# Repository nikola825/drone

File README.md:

## 3D printable FPV quadcopter frame, SMT32-based flight controller and flight controller code

Hobby project, a homemade FPV drone with custom flight controller and frame.

### Current version - master branch
Folder contents (see readmes for more details):
- `3dp` - Freecad projects with 3D printable drone parts
- `code` - code for the flight controller
- `hardware` - KiCad projects for flight controller and esc PCB

Off the shelf parts you'll need:
- screws and screw related parts for the frame - see the readme in `3dp`
- motors and propellers
- ESC
- ELRS receiver
- Camera and VTX if you want FPV video

I couldn't be bothered to do in-detail docs, feel free to email me at (reverse the string to get my email) `moc.liamg@528alokin`

Do not use for anything serious, this was made by a man who started with zero knowledge of electronics, embedded development, rust development, flight controllers and 3D print design.
If you need something reliable, just get off-the-shelf stuff.

### Older versions
- `droneV1` branch contains the old Arduino-as-a-controller + MPU6050 version
- `droneV2` branch contains the old ATMEGA2560 flight controller board with an onboard MPU6050
- `droneV3` branch contains the work-in-progress version of the STM32F411 flight controller

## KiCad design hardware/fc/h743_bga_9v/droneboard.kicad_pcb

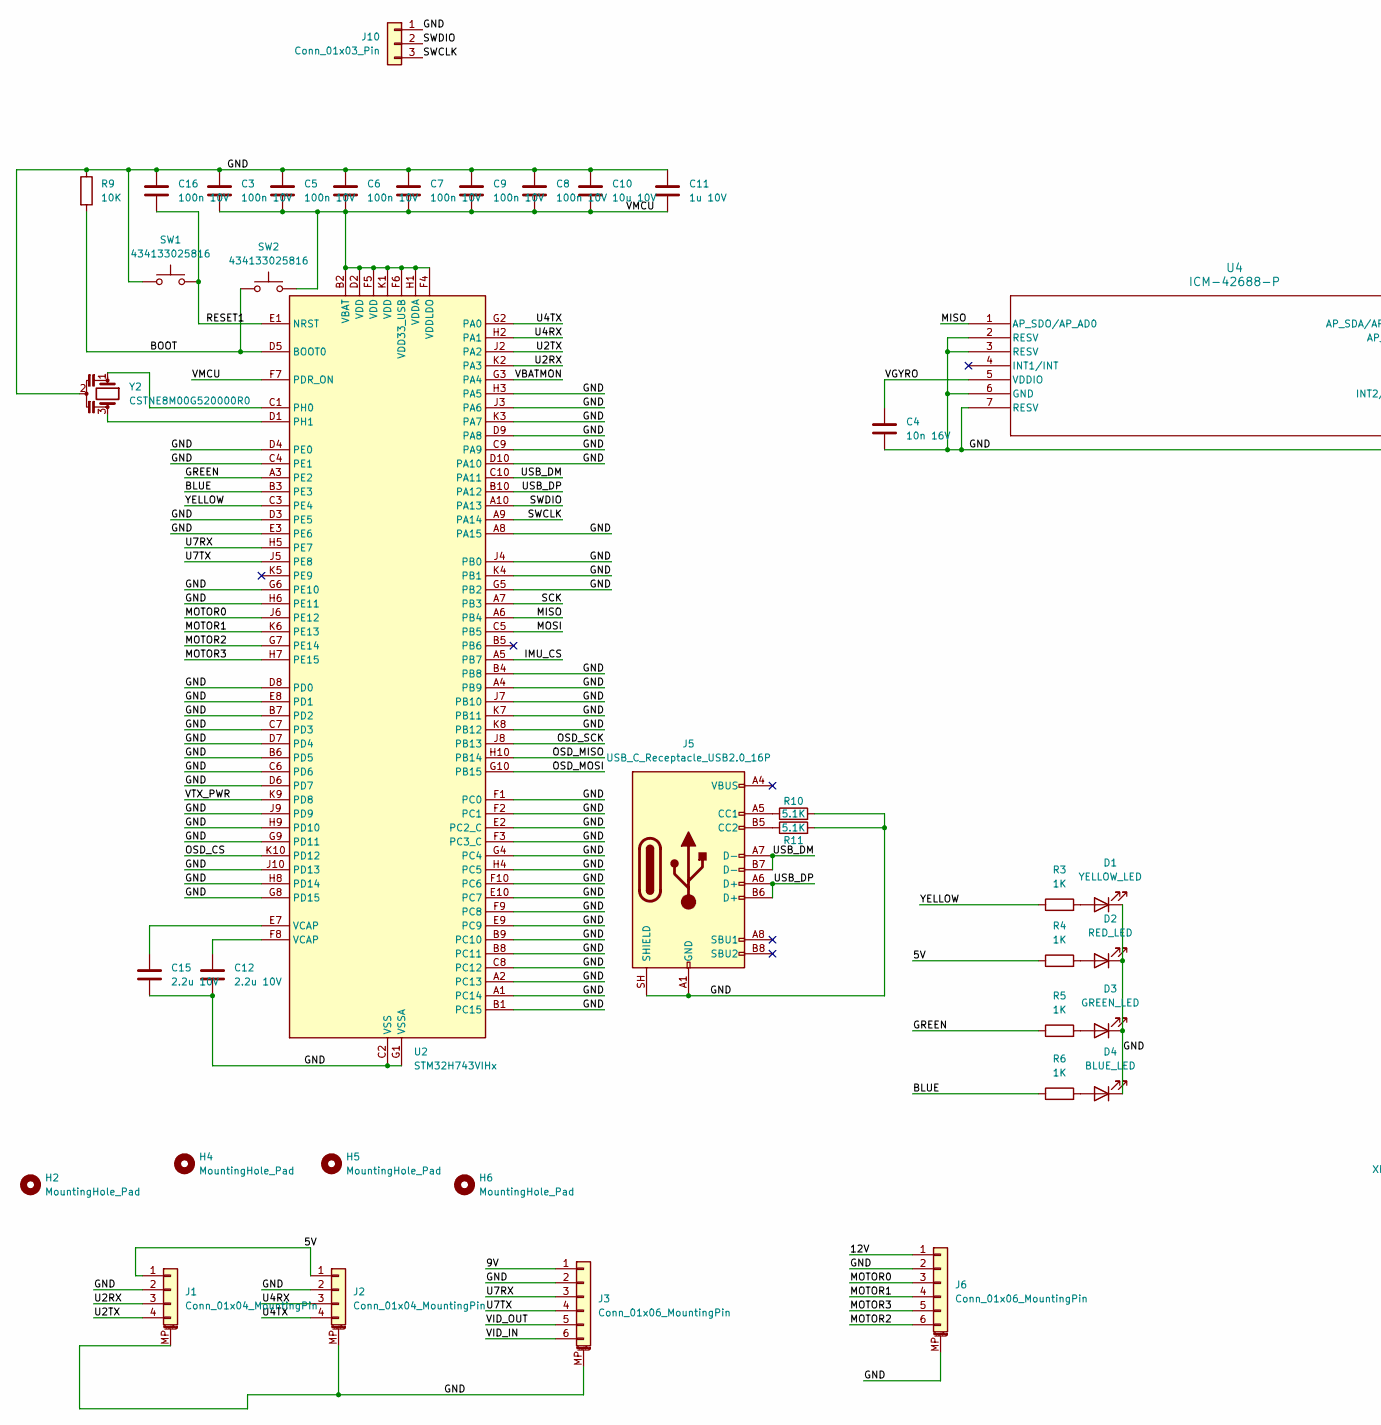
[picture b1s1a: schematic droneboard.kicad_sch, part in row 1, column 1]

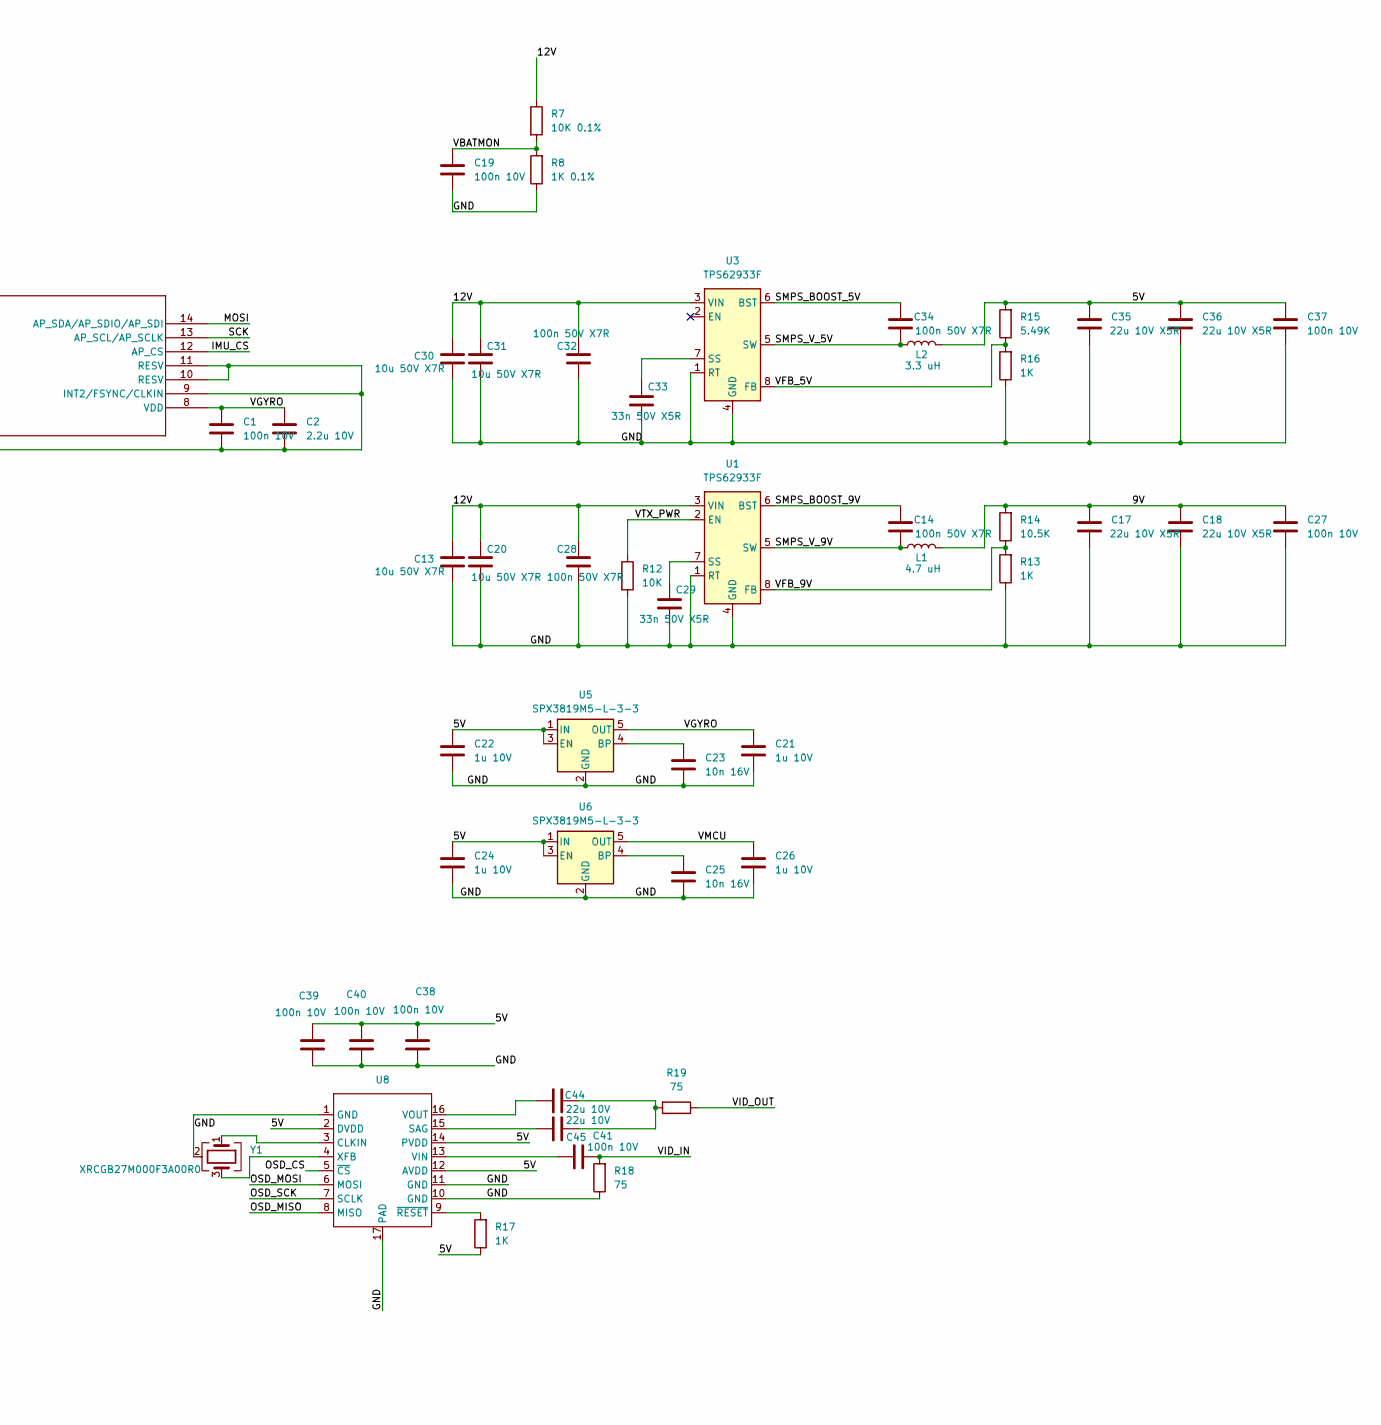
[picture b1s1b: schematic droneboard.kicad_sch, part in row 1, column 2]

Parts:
C1, C3, C5, C6, C7, C8, C9, C16, C19, C27, C37, C38, C39, C40, C41: 100n 10V; C_0201_0603Metric
C2, C12, C15: 2.2u 10V; C_0201_0603Metric
C4, C23, C25: 10n 16V; C_0201_0603Metric
C10: 10u 10V; C_0603_1608Metric
C11, C21, C22, C24, C26: 1u 10V; C_0201_0603Metric
C13, C20, C30, C31: 10u 50V X7R; C_1210_3225Metric
C14, C28, C32, C34: 100n 50V X7R; C_0402_1005Metric
C17, C18, C35, C36: 22u 10V X5R; C_0805_2012Metric
C29, C33: 33n 50V X5R; C_0402_1005Metric
C44, C45: 22u 10V; C_0603_1608Metric
D1: YELLOW_LED; LED_0603_1608Metric
D2: RED_LED; LED_0603_1608Metric
D3: GREEN_LED; LED_0603_1608Metric
D4: BLUE_LED; LED_0603_1608Metric
H2, H4, H5, H6: MountingHole_Pad; M3VibrationMount
J1, J2: Conn_01x04_MountingPin; JST_SH_SM04B-SRSS-TB_1x04-1MP_P1.00mm_Horizontal
J3, J6: Conn_01x06_MountingPin; JST_SH_SM06B-SRSS-TB_1x06-1MP_P1.00mm_Horizontal
J5: USB_C_Receptacle_USB2.0_16P; GCT_USB4110
J10: Conn_01x03_Pin; PinHeader_1x03_P2.00mm_Vertical
L1: 4.7 uH; L_Bourns_4040
L2: 3.3 uH; L_Bourns_4040
R3, R4, R5, R6, R13, R16, R17: 1K; R_0402_1005Metric
R7: 10K 0.1%; R_0603_1608Metric
R8: 1K 0.1%; R_0603_1608Metric
R9, R12: 10K; R_0201_0603Metric
R10, R11: 5.1K; R_0201_0603Metric
R14: 10.5K; R_0402_1005Metric
R15: 5.49K; R_0402_1005Metric
R18, R19: 75; R_0402_1005Metric
SW1, SW2: 434133025816; SW_Push_1P1T_NO_Vertical_Wuerth_434133025816
U1, U3: TPS62933F; SOT-583-8
U2: STM32H743VIHx; TFBGA-100_8x8mm_Layout10x10_P0.8mm
U4: ICM-42688-P; ICM42688_Custom
U5, U6: SPX3819M5-L-3-3; SOT-23-5
U8: AT7456ELAH
Y1: XRCGB27M000F3A00R0; Crystal_SMD_2016-4Pin_2.0x1.6mm
Y2: CSTNE8M00G520000R0; Resonator_SMD_Murata_CSTxExxV-3Pin_3.0x1.1mm

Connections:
/5V: C22.1, C24.1, C35.1, C36.1, C37.2, C38.2, C39.2, C40.2, J1.1, J2.1, L2.2, R4.1, R15.2, R17.1, U5.1 (IN), U5.3 (EN), U6.1 (IN), U6.3 (EN), U8.2 (DVDD), U8.12 (AVDD), U8.14 (PVDD)
/9V: C17.1, C18.1, C27.2, J3.1, L1.2, R14.2
/12V: C13.1, C20.1, C28.2, C30.1, C31.1, C32.2, J6.1, R7.1, U1.3 (VIN), U3.3 (VIN)
/BLUE: R6.1, U2.B3 (PE3)
/BOOT: R9.2, SW2.1, U2.D5 (BOOT0)
/GND: C1.1, C2.2, C3.2, C4.1, C5.2, C6.2, C7.2, C8.2, C9.2, C10.1, C11.1, C12.2, C13.2, C15.2, C16.2, C17.2, C18.2, C19.1, C20.2, C21.2, C22.2, C23.1, C24.2, C25.1, C26.2, C27.1, C28.1, C29.1, C30.2, C31.2, C32.1, C33.1, C35.2, C36.2, C37.1, C38.1, C39.1, C40.1, D1.1 (K), D2.1 (K), D3.1 (K), D4.1 (K), J1.2, J1.MP (MountPin), J2.2, J2.MP (MountPin), J3.2, J3.MP (MountPin), J5.A1 (GND), J5.A12 (GND), J5.B1 (GND), J5.B12 (GND), J5.SH (SHIELD), J6.2, J6.MP (MountPin), J10.1, R8.1, R9.1, R10.2, R11.2, R12.2, R13.1, R16.1, R18.1, SW1.2, U1.1 (RT), U1.4 (GND), U2.A1 (PC14), U2.A2 (PC13), U2.A4 (PB9), U2.A8 (PA15), U2.B1 (PC15), U2.B4 (PB8), U2.B6 (PD5), U2.B7 (PD2), U2.B8 (PC11), U2.B9 (PC10), U2.C2 (VSS), U2.C4 (PE1), U2.C6 (PD6), U2.C7 (PD3), U2.C8 (PC12), U2.C9 (PA9), U2.D3 (PE5), U2.D4 (PE0), U2.D6 (PD7), U2.D7 (PD4), U2.D8 (PD0), U2.D9 (PA8), U2.D10 (PA10), U2.E2 (PC2_C), U2.E3 (PE6), U2.E4 (VSS), U2.E5 (VSS), U2.E6 (VSS), U2.E8 (PD1), U2.E9 (PC9), U2.E10 (PC7), U2.F1 (PC0), U2.F2 (PC1), U2.F3 (PC3_C), U2.F9 (PC8), U2.F10 (PC6), U2.G1 (VSSA), U2.G4 (PC4), U2.G5 (PB2), U2.G6 (PE10), U2.G8 (PD15), U2.G9 (PD11), U2.H3 (PA5), U2.H4 (PC5), U2.H6 (PE11), U2.H8 (PD14), U2.H9 (PD10), U2.J1 (VSS), U2.J3 (PA6), U2.J4 (PB0), U2.J7 (PB10), U2.J9 (PD9), U2.J10 (PD13), U2.K3 (PA7), U2.K4 (PB1), U2.K7 (PB11), U2.K8 (PB12), U3.1 (RT), U3.4 (GND), U4.2 (RESV), U4.3 (RESV), U4.6 (GND), U4.7 (RESV), U4.9 (INT2/FSYNC/CLKIN), U4.10 (RESV), U4.11 (RESV), U5.2 (GND), U6.2 (GND), U8.1 (GND), U8.10 (GND), U8.11 (GND), U8.17 (PAD), Y1.2 (G), Y1.4 (G), Y2.2
/GREEN: R5.1, U2.A3 (PE2)
/IMU_CS: U2.A5 (PB7), U4.12 (AP_CS)
/MISO: U2.A6 (PB4), U4.1 (AP_SDO/AP_AD0)
/MOSI: U2.C5 (PB5), U4.14 (AP_SDA/AP_SDIO/AP_SDI)
/MOTOR0: J6.3, U2.J6 (PE12)
/MOTOR1: J6.4, U2.K6 (PE13)
/MOTOR2: J6.6, U2.G7 (PE14)
/MOTOR3: J6.5, U2.H7 (PE15)
/OSD_CS: U2.K10 (PD12), U8.5 (~CS)
/OSD_MISO: U2.H10 (PB14), U8.8 (MISO)
/OSD_MOSI: U2.G10 (PB15), U8.6 (MOSI)
/OSD_SCK: U2.J8 (PB13), U8.7 (SCLK)
/RESET1: C16.1, SW1.1, U2.E1 (NRST)
/SCK: U2.A7 (PB3), U4.13 (AP_SCL/AP_SCLK)
/SMPS_BOOST_5V: C34.2, U3.6 (BST)
/SMPS_BOOST_9V: C14.2, U1.6 (BST)
/SMPS_V_5V: C34.1, L2.1, U3.5 (SW)
/SMPS_V_9V: C14.1, L1.1, U1.5 (SW)
/SWCLK: J10.3, U2.A9 (PA14)
/SWDIO: J10.2, U2.A10 (PA13)
/U2RX: J1.3, U2.K2 (PA3)
/U2TX: J1.4, U2.J2 (PA2)
/U4RX: J2.3, U2.H2 (PA1)
/U4TX: J2.4, U2.G2 (PA0)
/U7RX: J3.3, U2.H5 (PE7)
/U7TX: J3.4, U2.J5 (PE8)
/USB_DM: J5.A7 (D-), J5.B7 (D-), U2.C10 (PA11)
/USB_DP: J5.A6 (D+), J5.B6 (D+), U2.B10 (PA12)
/VBATMON: C19.2, R7.2, R8.2, U2.G3 (PA4)
/VFB_5V: R15.1, R16.2, U3.8 (FB)
/VFB_9V: R13.2, R14.1, U1.8 (FB)
/VGYRO: C1.2, C2.1, C4.2, C21.1, U4.5 (VDDIO), U4.8 (VDD), U5.5 (OUT)
/VID_IN: C41.1, J3.6, R18.2
/VID_OUT: J3.5, R19.1
/VMCU: C3.1, C5.1, C6.1, C7.1, C8.1, C9.1, C10.2, C11.2, C26.1, SW2.2, U2.B2 (VBAT), U2.D2 (VDD), U2.F4 (VDDLDO), U2.F5 (VDD), U2.F6 (VDD33_USB), U2.F7 (PDR_ON), U2.H1 (VDDA), U2.K1 (VDD), U6.5 (OUT)
/VTX_PWR: R12.1, U1.2 (EN), U2.K9 (PD8)
/YELLOW: R3.1, U2.C3 (PE4)
unnamed: C12.1, U2.F8 (VCAP)
unnamed: C15.1, U2.E7 (VCAP)
unnamed: C44.2, C45.2, R19.2
unnamed: D1.2 (A), R3.2
unnamed: D2.2 (A), R4.2
unnamed: D3.2 (A), R5.2
unnamed: D4.2 (A), R6.2
unnamed: J5.A5 (CC1), R10.1
unnamed: J5.B5 (CC2), R11.1
unnamed: C29.2, U1.7 (SS)
unnamed: U2.C1 (PH0), Y2.1
unnamed: U2.D1 (PH1), Y2.3
unnamed: C33.2, U3.7 (SS)
unnamed: C23.2, U5.4 (BP)
unnamed: C25.2, U6.4 (BP)
unnamed: U8.3 (CLKIN), Y1.1
unnamed: C45.1, U8.15 (SAG)
unnamed: C41.2, U8.13 (VIN)
unnamed: C44.1, U8.16 (VOUT)
unnamed: U8.4 (XFB), Y1.3
unnamed: R17.2, U8.9 (~RESET)

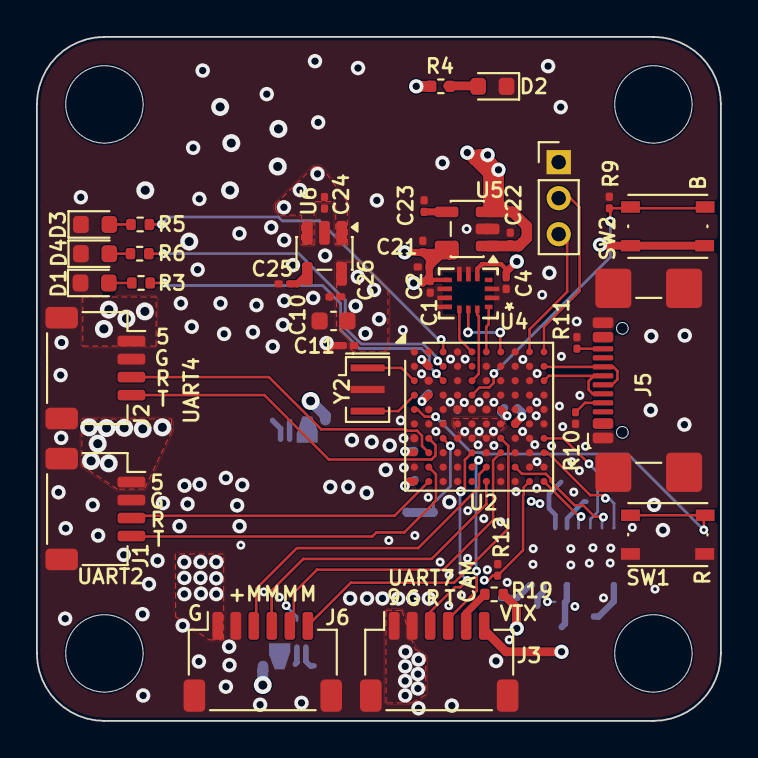
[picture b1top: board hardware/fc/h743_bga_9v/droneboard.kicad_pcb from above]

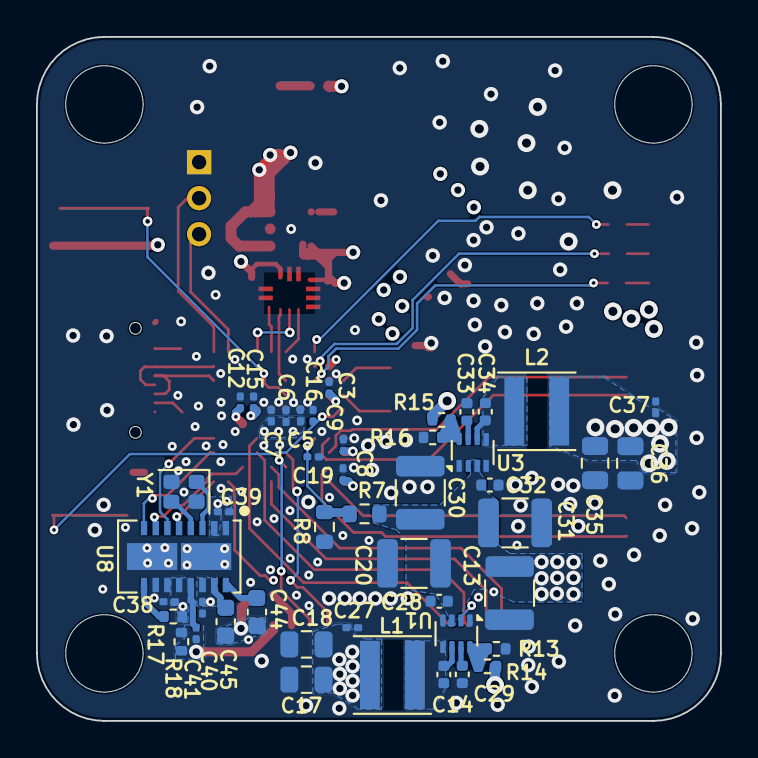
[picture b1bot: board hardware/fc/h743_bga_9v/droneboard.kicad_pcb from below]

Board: 4 copper layers, 38.0 x 38.0 mm, 87 parts (46 on the bottom side), 64 nets.

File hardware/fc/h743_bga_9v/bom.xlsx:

|  |  | xxxx xxxx xxxxx xxPCS BOM (Sample Bill of Materials)
Item # | *Designator | *Qty | Manufacturer | *Mfg Part # | Description / Value | *Package/Footprint | Type | Your Instructions / Notes
1 | C1, C3, C5, C6, C7, C8, C9, C16, C19, C27, C37 | 11 | Murata | GRM033R61A104KE15D | CAP CER 100nF 10V X5R 0201 | 0201 | SMD
2 | C2, C12, C15 | 3 | Murata | GRM033R61A225ME47D | CAP CER 2.2uF 10V X5R 0201 | 0201 | SMD
3 | C4, C23, C25 | 3 | Murata | GRM033R61C103KA12D | CAP CER 10nF 16V X5R 0201 | 0201 | SMD
4 | C10 | 1 | Samsung | CL10A106KP8NNNC | CAP CER 10uF 10V X5R 0603 | 0603 | SMD
5 | C11, C21, C22, C24, C26 | 5 | Murata | GRM033R61A105ME44D | CAP CER 1uF 10V X5R 0201 | 0201 | SMD
6 | C13, C20, C30, C31 | 4 | Samsung | CL32B106KBJNNNE | CAP CER 10uF 50V X7R 1210 | 1210 | SMD
7 | C14, C28, C32, C34 | 4 | Murata | GRM155R71H104KE14D | CAP CER 100nF 50V X7R 0402 | 0402 | SMD
8 | C17, C18, C35, C36 | 4 | Samsung | CL21A226MPQNNNE | CAP CER 22uF 10V X5R 0805 | 0805 | SMD
9 | C29, C33 | 2 | Murata | GRM155R71H333KE14D | CAP CER 33nF 50V X7R 0402 | 0402 | SMD
10 | D1 | 1 | Foshan NationStar | NCD0603Y5 | LED SMD Yellow 2V 20ma 0603 | 0603 | SMD
11 | D2 | 1 | Foshan NationStar | NCD0603R1 | LED SMD Red 2V 20ma 0603 | 0603 | SMD
12 | D3 | 1 | Foshan NationStar | NCD0603G3 | LED SMD Green 2V 20ma 0603 | 0603 | SMD
13 | D4 | 1 | Foshan NationStar | NCD0603B5 | LED SMD Blue 2V 20ma 0603 | 0603 | SMD
14 | J1, J2 | 2 | JST | SM04B-SRSS-TB | JST SH Headers SMT SIDE 4-pin | JST SH 4-pin header | SMD
15 | J4 | 1 | JST | SM08B-SRSS-TB | JST SH Headers SMT SIDE 8-pin | JST SH 8-pin header | SMD
16 | J5 | 1 | GCT | USB4110-GF-A | USB Connectors USB Type C, 2.0, Rec, SMT , G/F, RA , Top Mnt, T & R | USB-C | SMD
17 | J6 | 1 | JST | SM06B-SRSS-TB | JST SH Headers SMT SIDE 6-pin | JST SH 6-pin header | SMD
18 | L1 | 1 | Bourns | SRP4030FA-4R7M | Power Inductors - SMD 4.7uH 20% 5.1A | Inductor SMD 4.1x4.1mm | SMD
19 | L2 | 1 | Bourns | SRP4030FA-3R3M | Power Inductors - SMD 3.3uH 20% 6.6A | Inductor SMD 4.1x4.1mm | SMD
20 | R3, R4, R5, R6, R13, R16 | 6 | Yageo | RC0402FR-071KL | RES 1K OHM 0.1W 1% 0402 | 0402 | SMD
21 | R7 | 1 | Yageo | RT0603BRD0710KL | RES 10K OHM 0.1W 0.1% 0603 | 0603 | SMD
22 | R8 | 1 | Yageo | RT0603BRD071KL | RES 1K OHM 0.1W 0.1% 0603 | 0603 | SMD
23 | R9, R12 | 2 | Yageo | RC0201FR-0710KL | RES 10K OHM 0.05W 1% 0201 | 0201 | SMD
24 | R10, R11 | 2 | Yageo | RC0201FR-075K1L | RES 5.1K OHM 0.05W 1% 0201 | 0201 | SMD
25 | R14 | 1 | Yageo | RC0402FR-0710K5L | RES 10.5K OHM 0.067W 1% 0402 | 0402 | SMD
26 | R15 | 1 | Yageo | RC0402FR-075K49L | RES 5.49K OHM 0.1W 1% 0402 | 0402 | SMD
27 | SW1, SW2 | 2 | Wurth Elektronik | 434133025816 | SWITCH TACTILE SPST-NO 0.05A 16V | Tactile switch 4.2x3.2mm | SMD
28 | U1, U3 | 2 | Texas Instruments | TPS62933FDRLR | Buck Switching Regulator IC Positive Adjustable 0.8V 1 Output 3A SOT-583 | SOT-583-8 | SMD
29 | U2 | 1 | STMicroelectronics | STM32H743VIH6 | ARM Microcontrollers - MCU High-performance, Arm Cortex-M7 MCU 2MBytes of Flash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 | TFBGA-100 | SMD
30 | U4 | 1 | TDK Invensense | ICM-42688-P | IMUs - Inertial Measurement Units 6 Axis IMU Motion Tracking | LGA-14 3x2.5 P0.5 | SMD | Do not wash with ultrasound
31 | U5, U6 | 2 | MaxLinear | SPX3819M5-L-3-3/TR | LDO Voltage Regulators 500mA LOW NOISE LDO 3.3V | SOT-23-5 | SMD
32 | Y2 | 1 | Murata | CSTNE8M00G520000R0 | 8MHz 10pF SMD3213-3P Ceramic Resonators | 3-SMD, Non-Standard | SMD
Need a quick and accurante quote? Need an efficient production? Please read SMT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
Click for Instructions on How to Create a BOM

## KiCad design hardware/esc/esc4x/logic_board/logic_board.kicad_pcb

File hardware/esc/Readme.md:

# ESC

This folder contains PCBs for a 1x and a 4x ESC.
Mostly inspired by the [AM32 reference hardware](https://github.com/am32-firmware/am32-wiki/tree/ad24a0f2b645dd5e00588bb1a56035153b24e888/docs/development)

AM32REF_F051 target can be flashed using standard AM32 flashing process.

## esc1x
Contains one PCB for a single  ESC with solder points for power, control signal and ST-Link connections.

## esc4x 
Contains two PCBs - a logic board and a power board.

The boards are supposed to be soldered together using the castellated edges on the logic board and pads on the power board.

#### Logic board
This PCB contains the microcontrollers and gate drivers for the 4x esc.

It has no high power requirements. Can be fabricated as a cheaper 1 Oz/ft^2 thickness PCB

#### Power board
This PCB contains the mosfets, capacitors, regulators and connections for external stuff.

It is supposed to handle high currents of the motors and should be made with thicker 2 Oz/ft^2 copper.

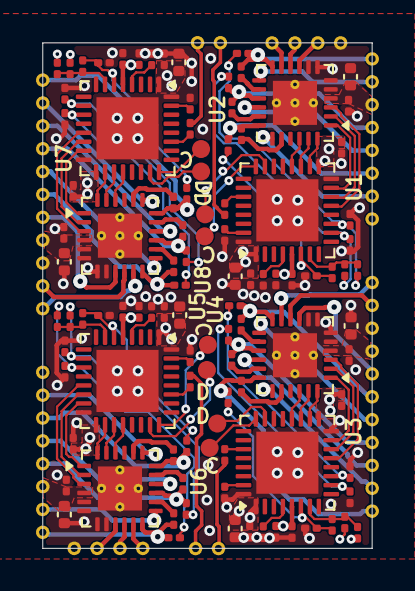
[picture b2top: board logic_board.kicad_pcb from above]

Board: 4 copper layers, 18.3 x 28.1 mm, 112 parts (0 on the bottom side), 119 nets.

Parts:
C1, C2, C3, C8, C12, C13, C14, C15, C17, C21, C25, C30, C34, C35, C36, C41: 100n 10V; C_0201_0603Metric
C4, C7, C16, C20, C26, C29, C37, C40: 10u 10V; C_0402_1005Metric
C5, C9, C10, C11, C18, C22, C23, C24, C27, C31, C32, C33, C38, C42, C43, C44: 1u 10V; C_0201_0603Metric
C6, C19, C28, C39: 10n 16V; C_0201_0603Metric
J1, J4: Conn_01x11; Castellated11Pin127
J2, J8: Conn_01x03; Castellated4Pin127
J3, J7: Conn_01x06; Castellated8Pin127
J5, J6: Conn_01x02; Castellated2Pin127
R1, R3, R5, R6, R8, R9, R11, R12, R13, R15, R16, R18, R20, R22, R23, R24, R26, R27, R29, R30, R32, R34, R36, R37, R39, R40, R42, R44: 10K; R_0201_0603Metric
R2, R4, R7, R10, R14, R17, R19, R21, R25, R28, R31, R33, R35, R38, R41, R43: 1K; R_0201_0603Metric
TP1, TP2, TP3, TP4, TP5, TP6, TP7, TP8: TestPoint; SW_Testpoint
U1, U3, U5, U7: STM32F051K8Ux; QFN-32-1EP_5x5mm_P0.5mm_EP3.45x3.45mm-Custom
U2, U4, U6, U8: DRV8300DRGE; VQFN-24-1EP_4x4mm_P0.5mm_EP2.45x2.45mm_ThermalVias-Custom

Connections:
/3V3_Left: C12.2, C13.2, C26.2, C27.1, C28.2, C34.2, C35.2, C37.2, C38.1, C39.2, J3.8, U5.1 (VDD), U5.5 (VDDA), U5.17 (VDD), U7.1 (VDD), U7.5 (VDDA), U7.17 (VDD)
/3V3_Right: C1.2, C2.2, C4.2, C5.1, C6.2, C14.2, C15.2, C16.2, C18.1, C19.2, J7.8, U1.1 (VDD), U1.5 (VDDA), U1.17 (VDD), U3.1 (VDD), U3.5 (VDDA), U3.17 (VDD)
/Esc1/5V: C20.2, C21.2, J7.3, U2.4 (GVDD)
/Esc1/AHIGH: U1.20 (PA10), U2.22 (INHA)
/Esc1/ALOW: U1.15 (PB1), U2.1 (INLA)
/Esc1/BEMFA: R3.2, R4.1, R5.1, U1.6 (PA0)
/Esc1/BEMFB: R6.2, R7.1, R8.1, U1.10 (PA4)
/Esc1/BEMFC: R9.2, R10.1, R11.1, U1.11 (PA5)
/Esc1/BEMF_COMMON: R3.1, R6.1, R9.1, U1.7 (PA1)
/Esc1/BHIGH: U1.19 (PA9), U2.23 (INHB)
/Esc1/BLOW: U1.14 (PB0), U2.2 (INLB)
/Esc1/BOOSTA: C22.2, U2.20 (BSTA)
/Esc1/BOOSTB: C23.2, U2.17 (BSTB)
/Esc1/BOOSTC: C24.2, U2.14 (BSTC)
/Esc1/BOOT0: R20.2, U1.31 (BOOT0)
/Esc1/CHIGH: U1.18 (PA8), U2.24 (INHC)
/Esc1/CLOW: U1.13 (PA7), U2.3 (INLC)
/Esc1/GHA: J7.7, U2.19 (GHA)
/Esc1/GHB: J7.5, U2.16 (GHB)
/Esc1/GHC: J7.2, U2.13 (GHC)
/Esc1/GLA: J8.1, U2.11 (GLA)
/Esc1/GLB: J8.2, U2.10 (GLB)
/Esc1/GLC: J8.3, U2.9 (GLC)
/Esc1/MOTORA: C22.1, J7.6, R5.2, U2.18 (SHA)
/Esc1/MOTORB: C23.1, J7.4, R8.2, U2.15 (SHB)
/Esc1/MOTORC: C24.1, J7.1, R11.2, U2.12 (SHC)
/Esc1/SIGNAL_INPUT: J6.1, R21.1
/Esc1/SWCLK: TP3.1, U1.24 (PA14)
/Esc1/SWDIO: TP1.1, U1.23 (PA13)
/Esc2/5V: C7.2, C8.2, J1.4, U4.4 (GVDD)
/Esc2/AHIGH: U3.20 (PA10), U4.22 (INHA)
/Esc2/ALOW: U3.15 (PB1), U4.1 (INLA)
/Esc2/BEMFA: R1.2, R2.1, R12.1, U3.6 (PA0)
/Esc2/BEMFB: R13.2, R14.1, R15.1, U3.10 (PA4)
/Esc2/BEMFC: R16.2, R17.1, R18.1, U3.11 (PA5)
/Esc2/BEMF_COMMON: R1.1, R13.1, R16.1, U3.7 (PA1)
/Esc2/BHIGH: U3.19 (PA9), U4.23 (INHB)
/Esc2/BLOW: U3.14 (PB0), U4.2 (INLB)
/Esc2/BOOSTA: C9.2, U4.20 (BSTA)
/Esc2/BOOSTB: C10.2, U4.17 (BSTB)
/Esc2/BOOSTC: C11.2, U4.14 (BSTC)
/Esc2/BOOT0: R22.2, U3.31 (BOOT0)
/Esc2/CHIGH: U3.18 (PA8), U4.24 (INHC)
/Esc2/CLOW: U3.13 (PA7), U4.3 (INLC)
/Esc2/GHA: J1.10, U4.19 (GHA)
/Esc2/GHB: J1.9, U4.16 (GHB)
/Esc2/GHC: J1.7, U4.13 (GHC)
/Esc2/GLA: J1.1, U4.11 (GLA)
/Esc2/GLB: J1.2, U4.10 (GLB)
/Esc2/GLC: J1.5, U4.9 (GLC)
/Esc2/MOTORA: C9.1, J1.11, R12.2, U4.18 (SHA)
/Esc2/MOTORB: C10.1, J1.8, R15.2, U4.15 (SHB)
/Esc2/MOTORC: C11.1, J1.6, R18.2, U4.12 (SHC)
/Esc2/SIGNAL_INPUT: J5.1, R19.1
/Esc2/SWCLK: TP2.1, U3.24 (PA14)
/Esc2/SWDIO: TP4.1, U3.23 (PA13)
/Esc3/5V: C29.2, C30.2, J3.3, U6.4 (GVDD)
/Esc3/AHIGH: U5.20 (PA10), U6.22 (INHA)
/Esc3/ALOW: U5.15 (PB1), U6.1 (INLA)
/Esc3/BEMFA: R24.2, R25.1, R26.1, U5.6 (PA0)
/Esc3/BEMFB: R27.2, R28.1, R29.1, U5.10 (PA4)
/Esc3/BEMFC: R30.2, R31.1, R32.1, U5.11 (PA5)
/Esc3/BEMF_COMMON: R24.1, R27.1, R30.1, U5.7 (PA1)
/Esc3/BHIGH: U5.19 (PA9), U6.23 (INHB)
/Esc3/BLOW: U5.14 (PB0), U6.2 (INLB)
/Esc3/BOOSTA: C31.2, U6.20 (BSTA)
/Esc3/BOOSTB: C32.2, U6.17 (BSTB)
/Esc3/BOOSTC: C33.2, U6.14 (BSTC)
/Esc3/BOOT0: R34.2, U5.31 (BOOT0)
/Esc3/CHIGH: U5.18 (PA8), U6.24 (INHC)
/Esc3/CLOW: U5.13 (PA7), U6.3 (INLC)
/Esc3/GHA: J3.7, U6.19 (GHA)
/Esc3/GHB: J3.5, U6.16 (GHB)
/Esc3/GHC: J3.2, U6.13 (GHC)
/Esc3/GLA: J2.1, U6.11 (GLA)
/Esc3/GLB: J2.2, U6.10 (GLB)
/Esc3/GLC: J2.3, U6.9 (GLC)
/Esc3/MOTORA: C31.1, J3.6, R26.2, U6.18 (SHA)
/Esc3/MOTORB: C32.1, J3.4, R29.2, U6.15 (SHB)
/Esc3/MOTORC: C33.1, J3.1, R32.2, U6.12 (SHC)
/Esc3/SIGNAL_INPUT: J5.2, R33.1
/Esc3/SWCLK: TP5.1, U5.24 (PA14)
/Esc3/SWDIO: TP6.1, U5.23 (PA13)
/Esc4/5V: C40.2, C41.2, J4.4, U8.4 (GVDD)
/Esc4/AHIGH: U7.20 (PA10), U8.22 (INHA)
/Esc4/ALOW: U7.15 (PB1), U8.1 (INLA)
/Esc4/BEMFA: R23.2, R35.1, R36.1, U7.6 (PA0)
/Esc4/BEMFB: R37.2, R38.1, R39.1, U7.10 (PA4)
/Esc4/BEMFC: R40.2, R41.1, R42.1, U7.11 (PA5)
/Esc4/BEMF_COMMON: R23.1, R37.1, R40.1, U7.7 (PA1)
/Esc4/BHIGH: U7.19 (PA9), U8.23 (INHB)
/Esc4/BLOW: U7.14 (PB0), U8.2 (INLB)
/Esc4/BOOSTA: C42.2, U8.20 (BSTA)
/Esc4/BOOSTB: C43.2, U8.17 (BSTB)
/Esc4/BOOSTC: C44.2, U8.14 (BSTC)
/Esc4/BOOT0: R44.2, U7.31 (BOOT0)
/Esc4/CHIGH: U7.18 (PA8), U8.24 (INHC)
/Esc4/CLOW: U7.13 (PA7), U8.3 (INLC)
/Esc4/GHA: J4.10, U8.19 (GHA)
/Esc4/GHB: J4.9, U8.16 (GHB)
/Esc4/GHC: J4.7, U8.13 (GHC)
/Esc4/GLA: J4.1, U8.11 (GLA)
/Esc4/GLB: J4.2, U8.10 (GLB)
/Esc4/GLC: J4.5, U8.9 (GLC)
/Esc4/MOTORA: C42.1, J4.11, R36.2, U8.18 (SHA)
/Esc4/MOTORB: C43.1, J4.8, R39.2, U8.15 (SHB)
/Esc4/MOTORC: C44.1, J4.6, R42.2, U8.12 (SHC)
/Esc4/SIGNAL_INPUT: J6.2, R43.1
/Esc4/SWCLK: TP7.1, U7.24 (PA14)
/Esc4/SWDIO: TP8.1, U7.23 (PA13)
GND: C1.1, C2.1, C3.2, C4.1, C5.2, C6.1, C7.1, C8.1, C12.1, C13.1, C14.1, C15.1, C16.1, C17.2, C18.2, C19.1, C20.1, C21.1, C25.2, C26.1, C27.2, C28.1, C29.1, C30.1, C34.1, C35.1, C36.2, C37.1, C38.2, C39.1, C40.1, C41.1, J1.3, J2.4, J4.3, J8.4, R2.2, R4.2, R7.2, R10.2, R14.2, R17.2, R20.1, R22.1, R25.2, R28.2, R31.2, R34.1, R35.2, R38.2, R41.2, R44.1, U1.16 (PB2), U1.32 (PB8), U1.33 (VSS), U2.5 (MODE), U2.6 (GND), U2.7 (NC), U2.8 (NC), U2.25 (PowerPAD), U3.16 (PB2), U3.32 (PB8), U3.33 (VSS), U4.5 (MODE), U4.6 (GND), U4.7 (NC), U4.8 (NC), U4.25 (PowerPAD), U5.16 (PB2), U5.32 (PB8), U5.33 (VSS), U6.5 (MODE), U6.6 (GND), U6.7 (NC), U6.8 (NC), U6.25 (PowerPAD), U7.16 (PB2), U7.32 (PB8), U7.33 (VSS), U8.5 (MODE), U8.6 (GND), U8.7 (NC), U8.8 (NC), U8.25 (PowerPAD)
unnamed: C17.1, U1.4 (NRST)
unnamed: R21.2, U1.27 (PB4)
unnamed: C3.1, U3.4 (NRST)
unnamed: R19.2, U3.27 (PB4)
unnamed: C25.1, U5.4 (NRST)
unnamed: R33.2, U5.27 (PB4)
unnamed: C36.1, U7.4 (NRST)
unnamed: R43.2, U7.27 (PB4)

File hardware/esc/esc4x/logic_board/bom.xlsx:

|  |  | xxxx xxxx xxxxx xxPCS BOM (Sample Bill of Materials)
Item # | *Designator | *Qty | Manufacturer | *Mfg Part # | Description / Value | *Package/Footprint | Type | Your Instructions / Notes
1 | R5,R39,R8,R3,R23,R18,R24,R37,R42,R27,R11,R26,R36,R20,R15,R9,R30,R13,R16,R6,R1,R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 | 28 | Yageo | RC0201FR-0710KL | RES 10K OHM 0.05W 1% 0201 | 0201 | SMD
2 | R38,R31,R41,R17,R14,R4,R7,R10,R2,R21,R25,R43,R28,R35,R33,R19 | 16 | Yageo | RC0201FR-071KL | RES 1K OHM 0.05W 1% 0201 | 0201 | SMD
3 | U3,U1,U7,U5 | 4 | STMicroelectronics | STM32F051K8U6TR | ARM Microcontrollers - MCU ARM Cortex-M0 MCU 64Kb Flash 48MHz | UFQFPN-32 | SMD
4 | C23,C5,C33,C9,C10,C18,C27,C32,C22,C31,C42,C43,C38,C11,C24,C44 | 16 | Murata | GRM033R61A105ME44D | CAP CER 1uF 10V X5R 0201 | 0201 | SMD
5 | C21,C2,C12,C3,C8,C35,C36,C1,C30,C14,C13,C17,C25,C15,C34,C41 | 16 | Murata | GRM033R61A104KE15D | CAP CER 100nF 10V X5R 0201 | 0201 | SMD
6 | C4,C7,C26,C40,C29,C37,C20,C16 | 8 | Samsung | CL05A106MP5NUNC | CAP CER 10uF 10V X5R 0402 | 0402 | SMD
7 | C19,C6,C39,C28 | 4 | Murata | GRM033R61C103KA12D | CAP CER 10nF 16V X5R 0201 | 0201 | SMD
8 | U6,U8,U2,U4 | 4 | Texas instruments | DRV8300DRGER | Gate Drivers 100-V max simple 3-p hase gate driver | VQFN-24 | SMD
Need a quick and accurante quote? Need an efficient production? Please read SMT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
Click for Instructions on How to Create a BOM

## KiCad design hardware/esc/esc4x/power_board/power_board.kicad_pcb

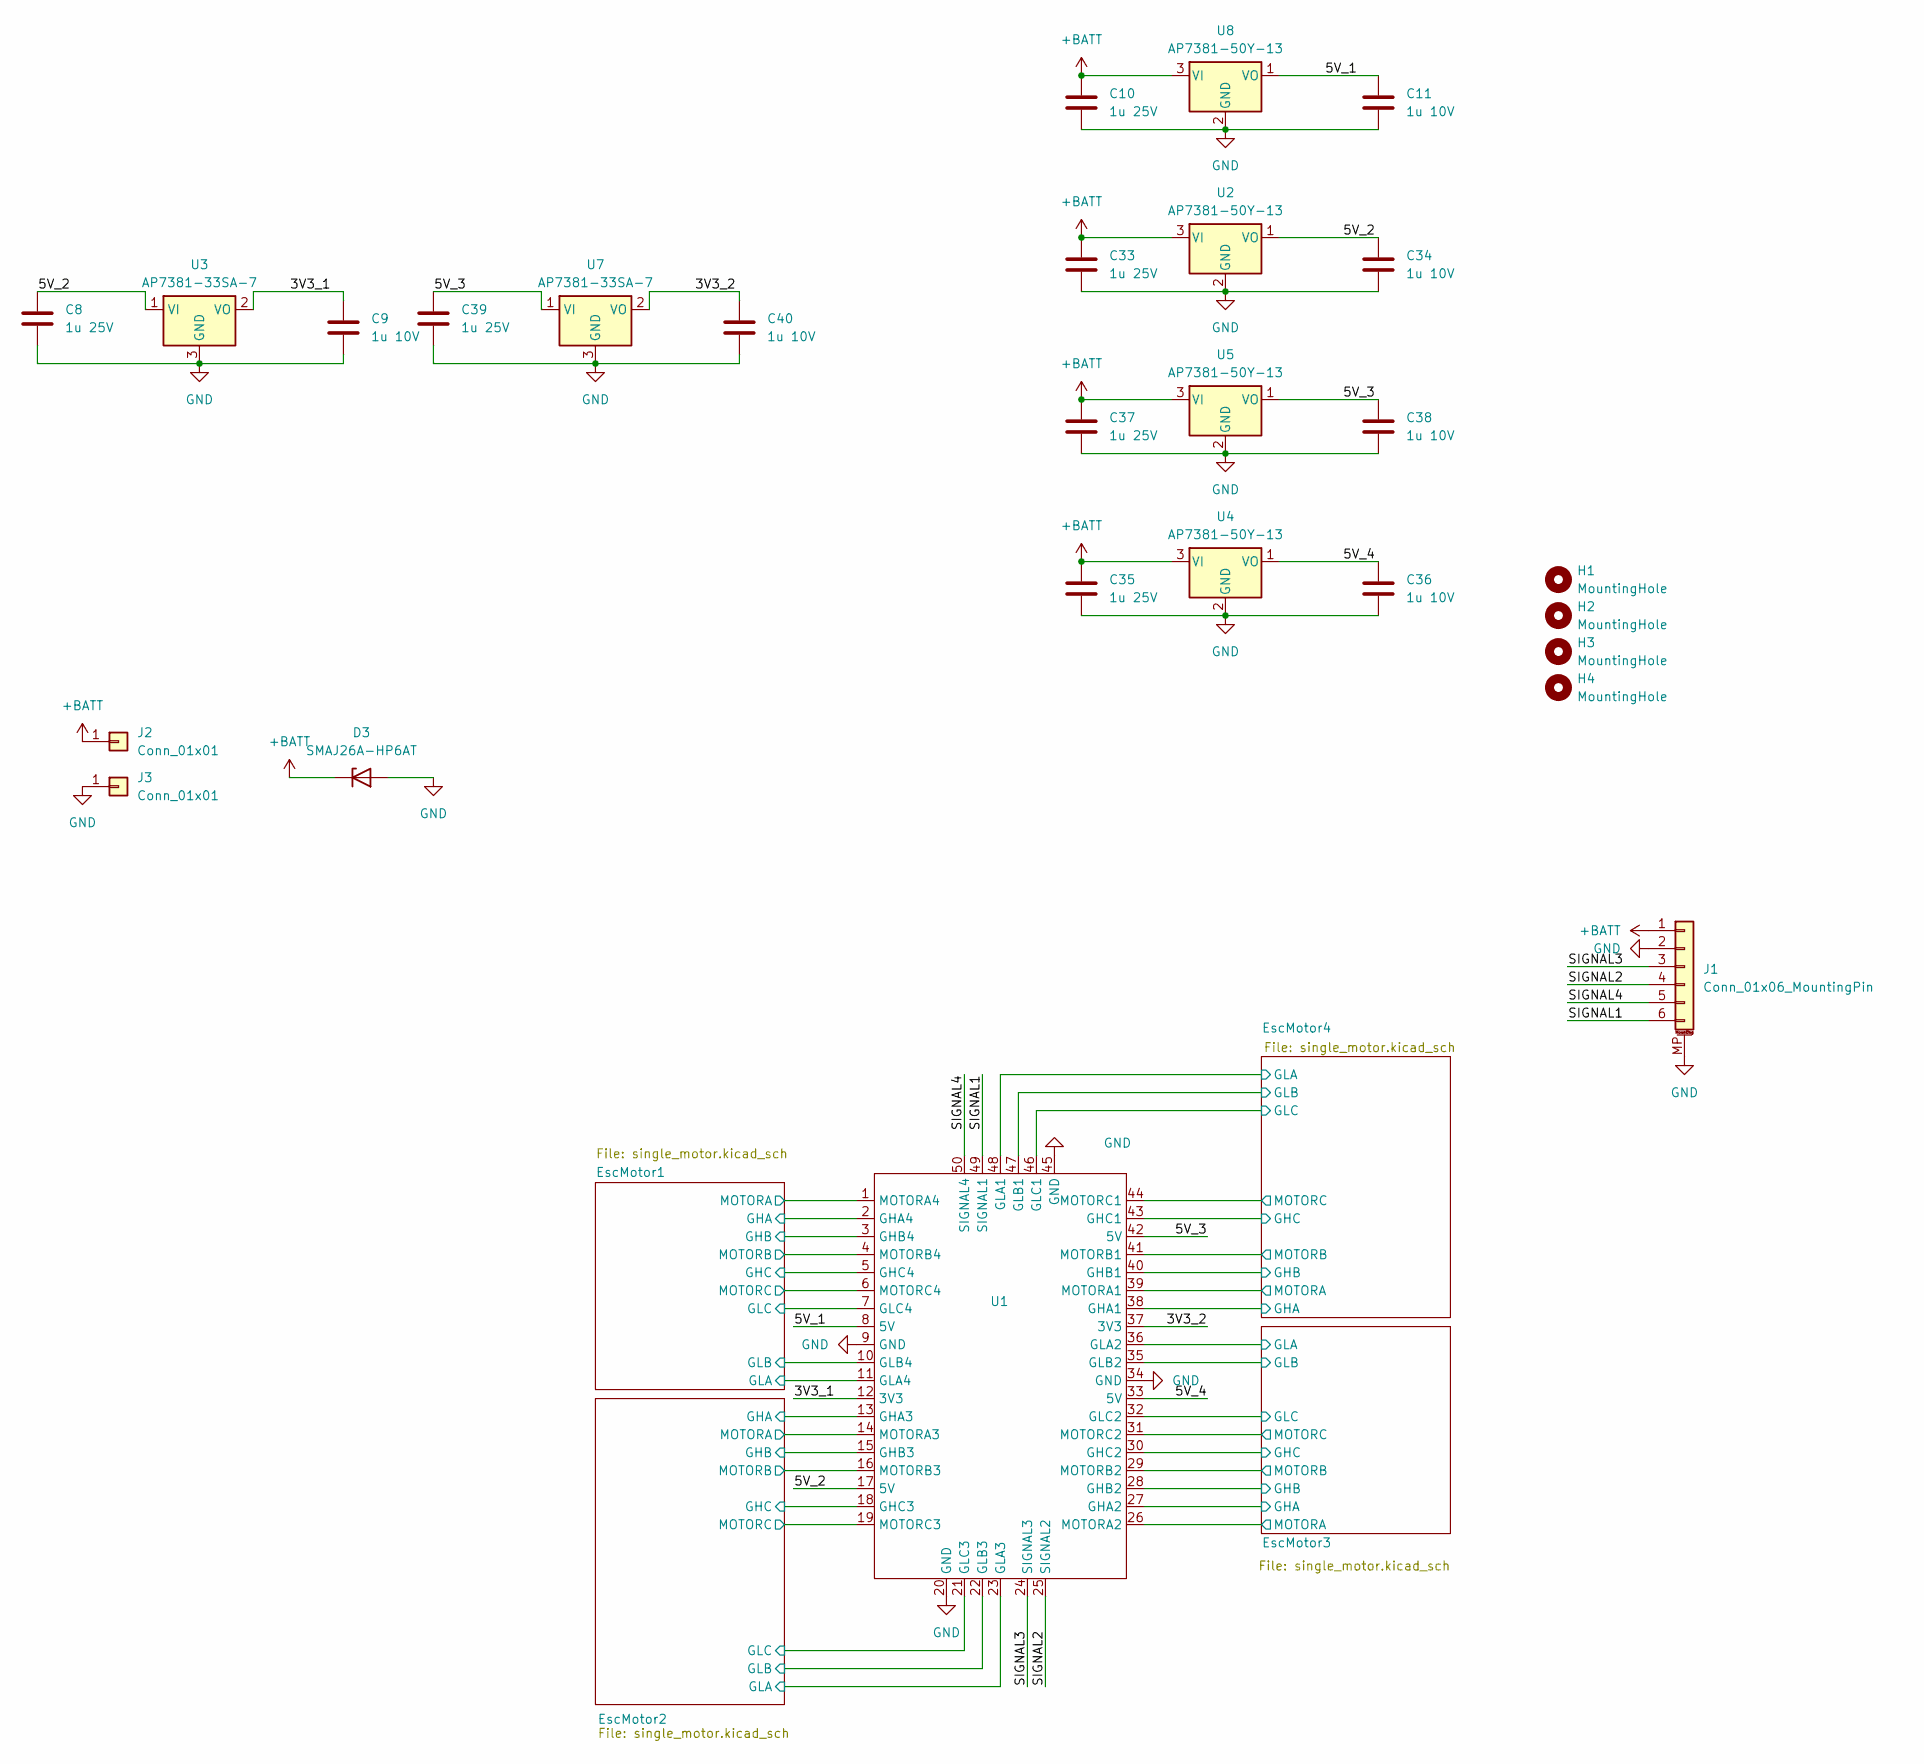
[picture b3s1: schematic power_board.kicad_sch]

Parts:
C8, C10, C33, C35, C37, C39: 1u 25V; C_0603_1608Metric
C9, C11, C34, C36, C38, C40: 1u 10V; C_0201_0603Metric
D3: SMAJ26A-HP6AT; D_SMA
H1, H2, H3, H4: MountingHole; EscScrewHole
J1: Conn_01x06_MountingPin; JST_SH_SM06B-SRSS-TB_1x06-1MP_P1.00mm_Horizontal
J2, J3: Conn_01x01; EscBatteryConnector
U1: LogicBoard
U2, U4, U5, U8: AP7381-50Y-13; SOT-89-3
U3, U7: AP7381-33SA-7; SOT-23

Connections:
+BATT: C10.1, C33.1, C35.1, C37.1, D3.1 (K), J1.1, J2.1 (Pin_1_1), U2.3 (VI), U4.3 (VI), U5.3 (VI), U8.3 (VI); also elsewhere on the board
/3V3_1: C9.1, U1.12 (3V3), U3.2 (VO)
/3V3_2: C40.1, U1.37 (3V3), U7.2 (VO)
/5V_1: C11.1, U1.8 (5V), U8.1 (VO)
/5V_2: C8.1, C34.1, U1.17 (5V), U2.1 (VO), U3.1 (VI)
/5V_3: C38.1, C39.1, U1.42 (5V), U5.1 (VO), U7.1 (VI)
/5V_4: C36.1, U1.33 (5V), U4.1 (VO)
/EscMotor1/GHA: U1.2 (GHA4); also elsewhere on the board
/EscMotor1/GHB: U1.3 (GHB4); also elsewhere on the board
/EscMotor1/GHC: U1.5 (GHC4); also elsewhere on the board
/EscMotor1/GLA: U1.11 (GLA4); also elsewhere on the board
/EscMotor1/GLB: U1.10 (GLB4); also elsewhere on the board
/EscMotor1/GLC: U1.7 (GLC4); also elsewhere on the board
/EscMotor1/MOTORA: U1.1 (MOTORA4); also elsewhere on the board
/EscMotor1/MOTORB: U1.4 (MOTORB4); also elsewhere on the board
/EscMotor1/MOTORC: U1.6 (MOTORC4); also elsewhere on the board
/EscMotor2/GHA: U1.13 (GHA3); also elsewhere on the board
/EscMotor2/GHB: U1.15 (GHB3); also elsewhere on the board
/EscMotor2/GHC: U1.18 (GHC3); also elsewhere on the board
/EscMotor2/GLA: U1.23 (GLA3); also elsewhere on the board
/EscMotor2/GLB: U1.22 (GLB3); also elsewhere on the board
/EscMotor2/GLC: U1.21 (GLC3); also elsewhere on the board
/EscMotor2/MOTORA: U1.14 (MOTORA3); also elsewhere on the board
/EscMotor2/MOTORB: U1.16 (MOTORB3); also elsewhere on the board
/EscMotor2/MOTORC: U1.19 (MOTORC3); also elsewhere on the board
/EscMotor3/GHA: U1.27 (GHA2); also elsewhere on the board
/EscMotor3/GHB: U1.28 (GHB2); also elsewhere on the board
/EscMotor3/GHC: U1.30 (GHC2); also elsewhere on the board
/EscMotor3/GLA: U1.36 (GLA2); also elsewhere on the board
/EscMotor3/GLB: U1.35 (GLB2); also elsewhere on the board
/EscMotor3/GLC: U1.32 (GLC2); also elsewhere on the board
/EscMotor3/MOTORA: U1.26 (MOTORA2); also elsewhere on the board
/EscMotor3/MOTORB: U1.29 (MOTORB2); also elsewhere on the board
/EscMotor3/MOTORC: U1.31 (MOTORC2); also elsewhere on the board
/EscMotor4/GHA: U1.38 (GHA1); also elsewhere on the board
/EscMotor4/GHB: U1.40 (GHB1); also elsewhere on the board
/EscMotor4/GHC: U1.43 (GHC1); also elsewhere on the board
/EscMotor4/GLA: U1.48 (GLA1); also elsewhere on the board
/EscMotor4/GLB: U1.47 (GLB1); also elsewhere on the board
/EscMotor4/GLC: U1.46 (GLC1); also elsewhere on the board
/EscMotor4/MOTORA: U1.39 (MOTORA1); also elsewhere on the board
/EscMotor4/MOTORB: U1.41 (MOTORB1); also elsewhere on the board
/EscMotor4/MOTORC: U1.44 (MOTORC1); also elsewhere on the board
/SIGNAL1: J1.6, U1.49 (SIGNAL1)
/SIGNAL2: J1.4, U1.25 (SIGNAL2)
/SIGNAL3: J1.3, U1.24 (SIGNAL3)
/SIGNAL4: J1.5, U1.50 (SIGNAL4)
GND: C8.2, C9.2, C10.2, C11.2, C33.2, C34.2, C35.2, C36.2, C37.2, C38.2, C39.2, C40.2, D3.2 (A), J1.2, J1.MP (MountPin), J3.1 (Pin_1_1), U1.9 (GND), U1.20 (GND), U1.34 (GND), U1.45 (GND), U2.2 (GND), U3.3 (GND), U4.2 (GND), U5.2 (GND), U7.3 (GND), U8.2 (GND); also elsewhere on the board
